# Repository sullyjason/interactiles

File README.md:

# Interactiles

[Portfolio Link](https://showspace.so/p/9350)

## Idea

Developing an interactive grid of buttons that light up and change colors when pressed, designed to communicate, connect, and create art across distances. Each grid is connected via the internet to a corresponding grid, allowing users to share visual messages in real-time.

## Prototyping

Until now, this project has served mostly as a platform for me to build on my coding and hardware skills. 

The current working prototype is a version with a 2x2 grid of RGB LED switches, connected to each other via an MQTT server.

The vision, of course, is a larger scale grid of clickable illuminated buttons. I am developing this with a modular approach, 4 tiles of 3x15 buttons controlled by a microcontroller that connects to the internet.

## To Do
- [x] Experiment with RGB Switches
- [x] Build hand-wired POC
- [x] Design PCB for 2x2 version
- [x] Assemble & test 2x2 version
- [x] Set up web server
- [x] Connect individual interactiles to web server
- [x] Web interface for monitoring
- [x] Large scale version module development (wip)
- [ ] Develop large scale version
- [ ] Design large scale modules
- [ ] Troubleshoot large scale modules
- [ ] Design miniature modules
- [ ] Enclosure for miniature modules
- [ ] Real world testing of 2x2 (in progress)

## Events

Exhibitions and real-world showings of Interactiles, each documented in its own folder under [`events/`](events/).

- [Zürich Decompression 2026](events/2026-decompression-zurich/) — two connected 5×3 grids in a fine-dining-inspired frame. Kraftwerk, Zürich, 9–11 October 2026.

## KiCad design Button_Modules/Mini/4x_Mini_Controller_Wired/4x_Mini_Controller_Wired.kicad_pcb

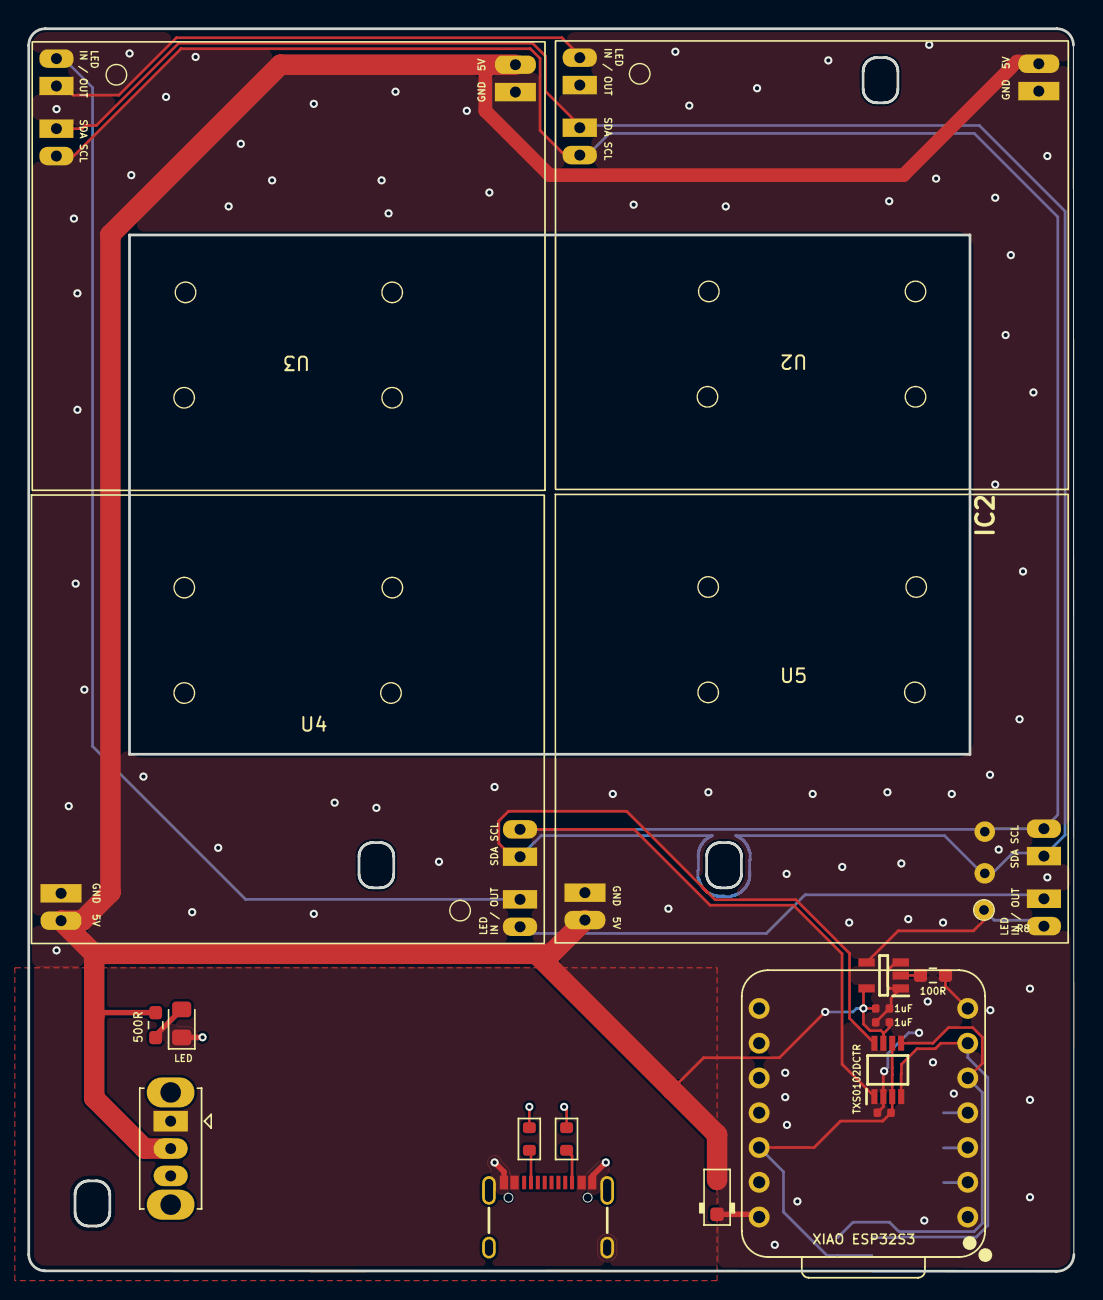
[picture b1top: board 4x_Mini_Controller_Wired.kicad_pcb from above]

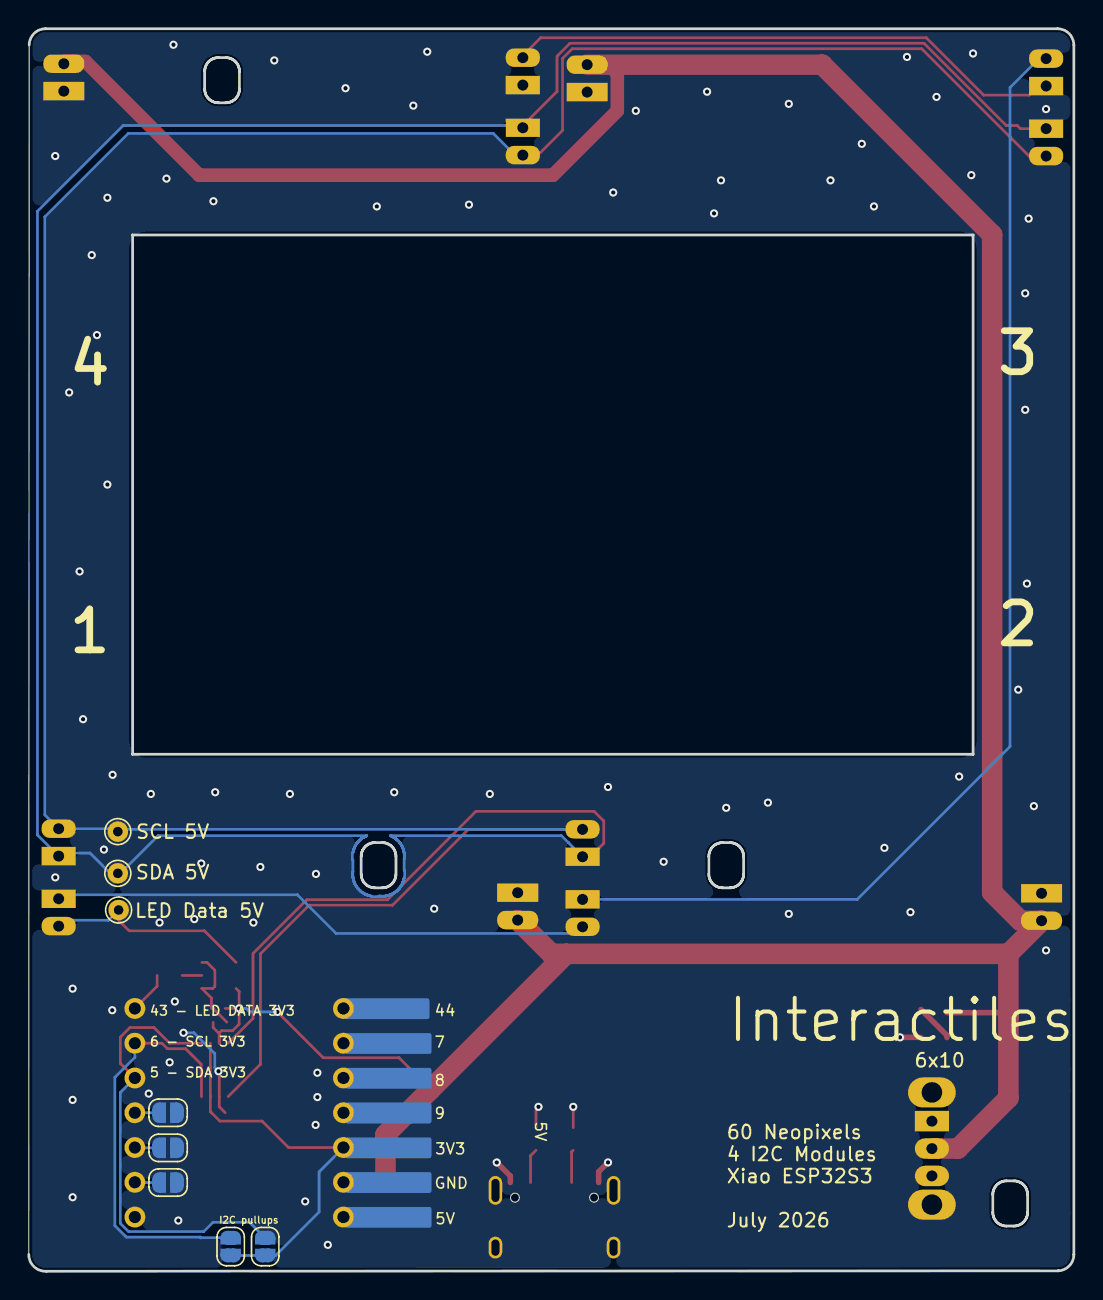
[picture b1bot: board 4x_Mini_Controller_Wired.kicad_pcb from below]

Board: 2 copper layers, 76.4 x 90.8 mm, 26 parts (8 on the bottom side), 21 nets.

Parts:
C2, C4, C7: 1uF; C_0402
D1: LED; LED_0805_2012Metric_Pad1.15x1.40mm_HandSolder
D6: 1N5817M; D_SOD-323_BigPads
IC2: TXS0102DCTR
IC3: SN74AHCT1G125DBVR
J2: USB_C_Receptacle; USB-C_16
JP1, JP2, JP5, JP6, JP7: SolderJumper_2_Open; SolderJumper-2_P1.3mm_Open_RoundedPad1.0x1.5mm
R1, R2: 5.1k; R_0603_1608Metric
R3: 500R; R_0603_1608Metric_Pad0.98x0.95mm_HandSolder
R8: 100R; R_0603_1608Metric_Pad0.98x0.95mm_HandSolder
SW5: Slide_Switch_SPDT; SW_Slide_SPDT_Straight_CK_OS102011MS2Q
TP3: SCL 5V; TestPoint_THTPad_D1.5mm_Drill0.7mm
TP4: SDA 5V; TestPoint_THTPad_D1.5mm_Drill0.7mm
TP5: LED Data 5V; TestPoint_THTPad_D1.5mm_Drill0.7mm
U2, U3, U4, U5: Mini_Module
U6: XIAO-ESP32-S3-SMD; XIAO-ESP32-S3-DIP

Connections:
+3V3: C4.1, IC2.3 (VCCA), IC2.6 (OE), JP6.2 (B), JP7.1 (A), U6.12 (3V3_OUT)
+5V: C2.1, C7.1, D6.2 (A), IC2.7 (VCCB), IC3.5 (VCC), R3.2, SW5.2, U2.5V, U3.5V, U4.5V, U5.5V
/5V to ESP32: D6.1 (K), U6.14 (VBUS)
/5V_TO_SWITCH: J2.VBUS, SW5.1
DATA_3v3: R8.1, U6.7 (D6)
DATA_5v: IC3.4 (Y), TP5.1 (1_1), U5.IN
DIP_1: JP1.1 (A), U6.2 (D1)
DIP_2: JP2.1 (A), U6.3 (D2)
DIP_3: JP5.1 (A), U6.4 (D3)
GND: C2.2, C4.2, C7.2, D1.1, IC2.2 (GND), IC3.1 (~OE), IC3.3 (GND), J2.GND, J2.S (SHIELD), JP1.2 (B), JP2.2 (B), JP5.2 (B), R1.2, R2.2, U2.GND, U3.GND, U4.GND, U5.GND, U6.13 (GND)
unnamed: D1.2, R3.1
unnamed: IC3.2 (A), R8.2
unnamed: J2.A5 (CC1), R1.1
unnamed: J2.B5 (CC2), R2.1
unnamed: U2.IN, U3.OUT
unnamed: U3.IN, U4.OUT
unnamed: U4.IN, U5.OUT
SCL_3v3: IC2.4 (A2), JP7.2 (B), U6.6 (D5)
SCL_5v: IC2.1 (B2), TP3.1 (1_1), U2.SCL, U3.SCL, U4.SCL, U5.SCL
SDA_3v3: IC2.5 (A1), JP6.1 (A), U6.5 (D4)
SDA_5v: IC2.8 (B1), TP4.1 (1_1), U2.SDA, U3.SDA, U4.SDA, U5.SDA

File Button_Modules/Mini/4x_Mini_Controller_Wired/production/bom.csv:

Designator,Footprint,Quantity,Value,LCSC Part #
"C2, C4, C7",C_0402,3,1uF,C52923
D1,0805,1,LED,
D6,D_SOD-323_BigPads,1,1N5817M,
IC2,TXS0102DCTR,1,TXS0102DCTR,
IC3,SN74AHCT1G125DBVR,1,SN74AHCT1G125DBVR,
J2,USB-C_16,1,USB_C_Receptacle,
"R1, R2",0603,2,5.1k,
R3,0603,1,500R,
R8,0603,1,100R,
SW5,SW_Slide_SPDT_Straight_CK_OS102011MS2Q,1,Slide_Switch_SPDT,
TP3,TestPoint_THTPad_D1.5mm_Drill0.7mm,1,SCL 5V,
TP4,TestPoint_THTPad_D1.5mm_Drill0.7mm,1,SDA 5V,
TP5,TestPoint_THTPad_D1.5mm_Drill0.7mm,1,LED Data 5V,
"U2, U3, U4, U5",Mini_Module,4,~,
U6,XIAO-ESP32-S3-DIP,1,XIAO-ESP32-S3-SMD,

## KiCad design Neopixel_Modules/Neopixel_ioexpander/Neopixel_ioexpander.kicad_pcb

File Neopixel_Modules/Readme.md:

# Modules of addressable RGB switch panels in various sizes

Configurations of 3x5 Switches to create a 15 pixel grid, listening for key interrupts via an MCP23017 i2c I/O expander. The switches are provided by Lakeview Electronics in Shenzhen. They are invididually addressable and compatible with the Neopixel library. 

## Large

Using the largest assembly of the manufacturer's PLB product line, measuring alost 3x3cm per switch. 15 switches routed to a FCP Connector, headers for LED data lines and screw terminals for 5V/ground.

## I/O Expander

Using a MCP23017. For use with the large module via the FPC connector or for other future switch modules. Reduces the 15 individual switch lines to two i2c lines. Using a dip switch to set the i2c address.

https://learn.adafruit.com/adafruit-mcp23017-i2c-gpio-expander
https://github.com/adafruit/Adafruit-MCP23017-Arduino-Library

## Mini

Using the smallest assembly of the manufacturer's TL1 product line, measuring only 7.5mm^2 per switch. the module is so tightly packed that the PCB had to be designed in 4 layers and the i/o expander is directly attached to the bottom of the switch grid. 
Pinout on i/o expander is not intuitive as a result, refer to schematic. 

## Controller (WIP)

Controller for a string of a maximum of 8 3x5 modules, using an ESP32.
- ESP32
- interfaces: i2c, LED data, common ground
- Charger, if battery power is used (make optional?) and USB-C port with PD circuit?
- On/off switch and small LED indicator
- Toggle switch for "Set" or "program" mode for configuration
- ?

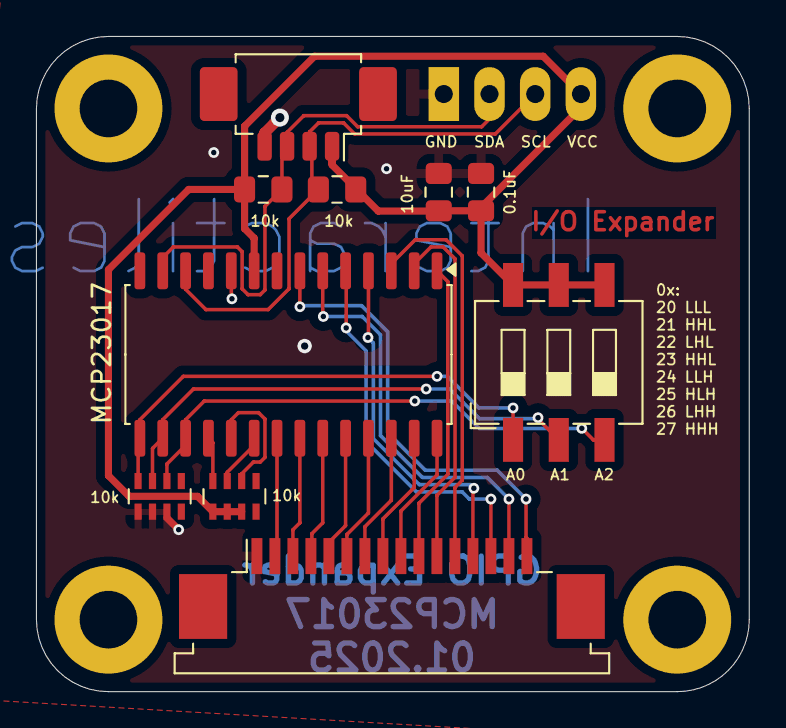
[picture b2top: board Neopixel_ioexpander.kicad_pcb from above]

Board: 2 copper layers, 39.6 x 36.4 mm, 15 parts (0 on the bottom side), 25 nets.

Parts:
0.1uF: 0.1uF; C_0805_2012Metric_Pad1.18x1.45mm_HandSolder
10k, 10k#2: R_Pack04; R_Array_Concave_4x0603
10k#3, 10k#4: 10k; C_0805_2012Metric_Pad1.18x1.45mm_HandSolder
10uF: 10uF; C_0805_2012Metric_Pad1.18x1.45mm_HandSolder
H1, H2, H3, H4: MountingHole_M3_3.2mm_Pad; MountingHole_3.2mm_Pad
J1: PINHD_1x16_Male; TE_1-84952-6_1x16-1MP_P1.0mm_Horizontal
J2: PINHD_1x4_Male; Molex_PicoBlade_53261-0471_1x04-1MP_P1.25mm_Horizontal
J3: PINHD_1x4_Male; PinHeader_1x04_P2.54mm_Vertical
MCP23017: MCP23017_SO; SOIC-28W_7.5x17.9mm_P1.27mm
SW2: SW_DIP_x03; SW_DIP_SPSTx03_Slide_6.7x9.18mm_W8.61mm_P2.54mm_LowProfile

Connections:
GND: 0.1uF.2, 10k#2.1 (R1.1), 10k#2.2 (R2.1), 10k#2.3 (R3.1), 10uF.2, J1.1, J2.4, J3.4, MCP23017.10 (VSS)
unnamed: 10k.2 (R2.1), MCP23017.19 (INTB)
unnamed: 10k.3 (R3.1), MCP23017.20 (INTA)
unnamed: 10k.4 (R4.1), MCP23017.18 (~RESET)
unnamed: 10k#2.8 (R1.2), MCP23017.15 (A0), SW2.1
unnamed: 10k#2.7 (R2.2), MCP23017.16 (A1), SW2.2
unnamed: 10k#2.6 (R3.2), MCP23017.17 (A2), SW2.3
SCL: 10k#4.1, J2.2, J3.2, MCP23017.12 (SCK)
SDA: 10k#3.1, J2.3, J3.3, MCP23017.13 (SDA)
SW1: J1.2, MCP23017.21 (GPA0)
SW2: J1.3, MCP23017.22 (GPA1)
SW3: J1.4, MCP23017.23 (GPA2)
SW4: J1.5, MCP23017.24 (GPA3)
SW5: J1.6, MCP23017.25 (GPA4)
SW6: J1.7, MCP23017.26 (GPA5)
SW7: J1.8, MCP23017.27 (GPA6)
SW8: J1.9, MCP23017.28 (GPA7)
SW9: J1.10, MCP23017.1 (GPB0)
SW10: J1.11, MCP23017.2 (GPB1)
SW11: J1.12, MCP23017.3 (GPB2)
SW12: J1.13, MCP23017.4 (GPB3)
SW13: J1.14, MCP23017.5 (GPB4)
SW14: J1.15, MCP23017.6 (GPB5)
SW15: J1.16, MCP23017.7 (GPB6)
VCC: 0.1uF.1, 10k.5 (R4.2), 10k.6 (R3.2), 10k.7 (R2.2), 10k#3.2, 10k#4.2, 10uF.1, J2.1, J3.1, MCP23017.9 (VDD), SW2.4, SW2.5, SW2.6

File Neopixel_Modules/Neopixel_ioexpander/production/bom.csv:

Designator,Footprint,Quantity,Value,LCSC Part #
0.1uF,0805,1,0.1uF,
"10k_4, 10k_3",R_Array_Concave_4x0603,2,R_Pack04,
"10k_2, 10k",0805,2,10k,
10uF,0805,1,10uF,
"H1, H2, H3, H4",MountingHole_3.2mm_Pad,4,MountingHole_M3_3.2mm_Pad,
J1,TE_1-84952-6_1x16-1MP_P1.0mm_Horizontal,1,PINHD_1x16_Male,
J2,Molex_PicoBlade_53261-0471_1x04-1MP_P1.25mm_Horizontal,1,PINHD_1x4_Male,
J3,PinHeader_1x04_P2.54mm_Vertical,1,PINHD_1x4_Male,
MCP23017,SOIC-28W_7.5x18.7mm_P1.27mm,1,MCP23017_ML,
SW2,SW_DIP_SPSTx03_Slide_6.7x9.18mm_W8.61mm_P2.54mm_LowProfile,1,SW_DIP_x03,

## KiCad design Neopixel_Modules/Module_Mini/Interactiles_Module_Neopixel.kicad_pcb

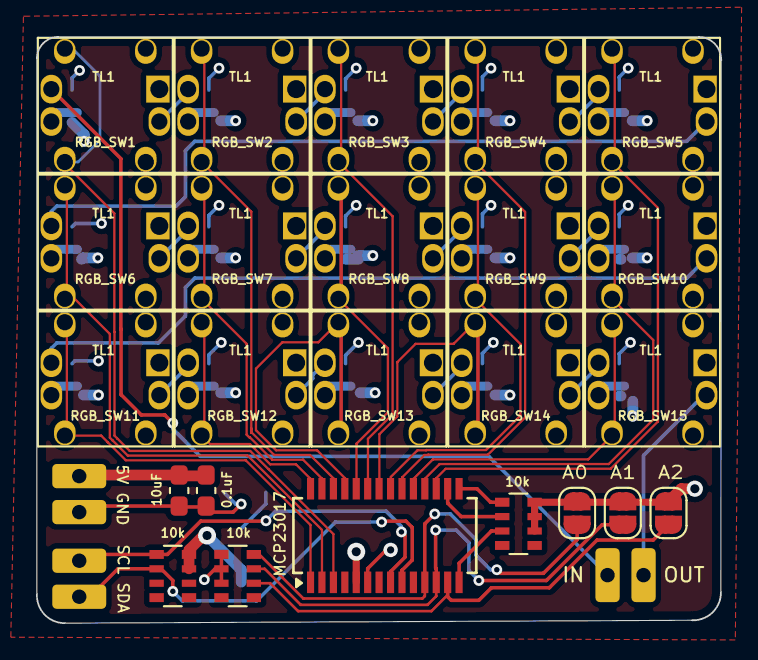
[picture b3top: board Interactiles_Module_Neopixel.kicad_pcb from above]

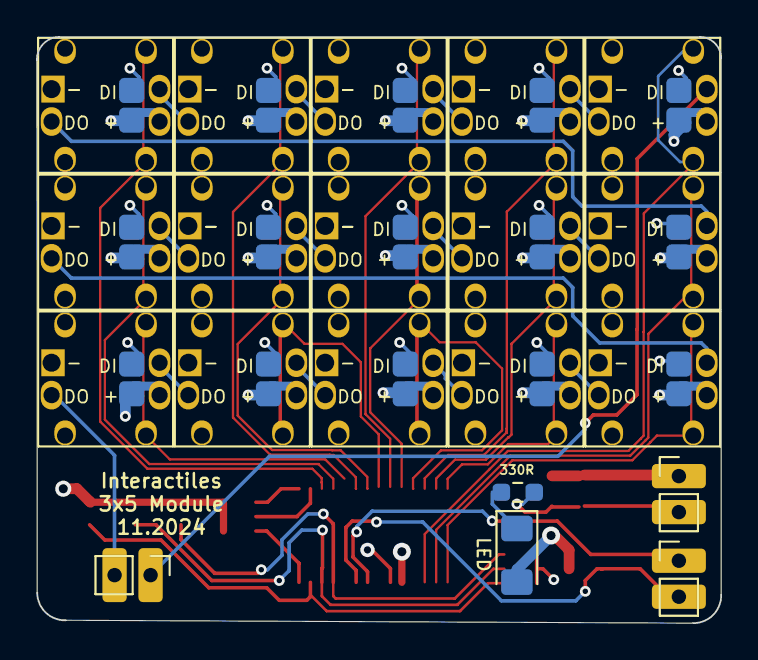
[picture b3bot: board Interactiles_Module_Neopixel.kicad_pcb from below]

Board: 4 copper layers, 38.0 x 32.6 mm, 29 parts (5 on the bottom side), 42 nets.

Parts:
10k, 10k#2: R_Pack04; R_Array_Convex_4x0603
C1: 10uF; C_0603_1608Metric_Pad1.08x0.95mm_HandSolder
C2: 0.1uF; C_0603_1608Metric_Pad1.08x0.95mm_HandSolder
J1: PINHD_1x2_Male; PinHeader_1x02_P2.00mm_Vertical
J2, J4: PINHD_1x2_Female; PinHeader_1x02_P2.00mm_Vertical
JP1, JP2, JP3: SolderJumper_2_Open; SolderJumper-2_P1.3mm_Open_RoundedPad1.0x1.5mm
LED: LED; LED_1206_3216Metric_Pad1.42x1.75mm_HandSolder
R1: 330R; R_0603_1608Metric_Pad0.98x0.95mm_HandSolder
RGB_SW1, RGB_SW2, RGB_SW3, RGB_SW4, RGB_SW5, RGB_SW6, RGB_SW7, RGB_SW8, RGB_SW9, RGB_SW10, RGB_SW11, RGB_SW12, RGB_SW13, RGB_SW14, RGB_SW15: PLB_RGB_SW; TL1_RBG_Adressable_1_mini
RN2: R_Pack04; R_Array_Convex_4x0603
U1: MCP23017_ML; SSOP-28_3.9x9.9mm_P0.635mm

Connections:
+5V: 10k.7 (R2.2), 10k.8 (R1.2), C1.1, C2.1, J1.1, JP1.2 (B), JP2.2 (B), JP3.2 (B), LED.2, RGB_SW1.VDD, RGB_SW2.VDD, RGB_SW3.VDD, RGB_SW4.VDD, RGB_SW5.VDD, RGB_SW6.VDD, RGB_SW7.VDD, RGB_SW8.VDD, RGB_SW9.VDD, RGB_SW10.VDD, RGB_SW11.VDD, RGB_SW12.VDD, RGB_SW13.VDD, RGB_SW14.VDD, RGB_SW15.VDD, RN2.6 (R3.2), RN2.7 (R2.2), RN2.8 (R1.2), U1.5 (VDD)
GND: 10k#2.1 (R1.1), 10k#2.2 (R2.1), 10k#2.3 (R3.1), C1.2, C2.2, J1.2, R1.2, RGB_SW1.GND, RGB_SW1.SW2, RGB_SW2.GND, RGB_SW2.SW2, RGB_SW3.GND, RGB_SW3.SW2, RGB_SW4.GND, RGB_SW4.SW2, RGB_SW5.GND, RGB_SW5.SW2, RGB_SW6.GND, RGB_SW6.SW2, RGB_SW7.GND, RGB_SW7.SW2, RGB_SW8.GND, RGB_SW8.SW2, RGB_SW9.GND, RGB_SW9.SW2, RGB_SW10.GND, RGB_SW10.SW2, RGB_SW11.GND, RGB_SW11.SW2, RGB_SW12.GND, RGB_SW12.SW2, RGB_SW13.GND, RGB_SW13.SW2, RGB_SW14.GND, RGB_SW14.SW2, RGB_SW15.GND, RGB_SW15.SW2, U1.6 (VSS)
LED_IN: J4.1, RGB_SW1.DI (DIN)
LED_OUT: J4.2, RGB_SW15.DO
unnamed: LED.1, R1.1
unnamed: 10k#2.8 (R1.2), JP1.1 (A), U1.11 (A0)
unnamed: 10k#2.7 (R2.2), JP2.1 (A), U1.12 (A1)
unnamed: 10k#2.6 (R3.2), JP3.1 (A), U1.13 (A2)
unnamed: RGB_SW1.DO, RGB_SW2.DI (DIN)
unnamed: RGB_SW2.DO, RGB_SW3.DI (DIN)
unnamed: RGB_SW3.DO, RGB_SW4.DI (DIN)
unnamed: RGB_SW4.DO, RGB_SW5.DI (DIN)
unnamed: RGB_SW5.DO, RGB_SW6.DI (DIN)
unnamed: RGB_SW6.DO, RGB_SW7.DI (DIN)
unnamed: RGB_SW7.DO, RGB_SW8.DI (DIN)
unnamed: RGB_SW8.DO, RGB_SW9.DI (DIN)
unnamed: RGB_SW9.DO, RGB_SW10.DI (DIN)
unnamed: RGB_SW10.DO, RGB_SW11.DI (DIN)
unnamed: RGB_SW11.DO, RGB_SW12.DI (DIN)
unnamed: RGB_SW12.DO, RGB_SW13.DI (DIN)
unnamed: RGB_SW13.DO, RGB_SW14.DI (DIN)
unnamed: RGB_SW14.DO, RGB_SW15.DI (DIN)
unnamed: RN2.1 (R1.1), U1.15 (INTB)
unnamed: RN2.2 (R2.1), U1.16 (INTA)
unnamed: RN2.3 (R3.1), U1.14 (~RESET)
SCL: 10k.1 (R1.1), J2.1, U1.8 (SCK)
SDA: 10k.2 (R2.1), J2.2, U1.9 (SDA)
SW1: RGB_SW1.SW1, U1.3 (GPB6)
SW2: RGB_SW2.SW1, U1.26 (GPB1)
SW3: RGB_SW3.SW1, U1.23 (GPA6)
SW4: RGB_SW4.SW1, U1.20 (GPA3)
SW5: RGB_SW5.SW1, U1.17 (GPA0)
SW6: RGB_SW6.SW1, U1.2 (GPB5)
SW7: RGB_SW7.SW1, U1.27 (GPB2)
SW8: RGB_SW8.SW1, U1.24 (GPA7)
SW9: RGB_SW9.SW1, U1.21 (GPA4)
SW10: RGB_SW10.SW1, U1.18 (GPA1)
SW11: RGB_SW11.SW1, U1.1 (GPB4)
SW12: RGB_SW12.SW1, U1.28 (GPB3)
SW13: RGB_SW13.SW1, U1.25 (GPB0)
SW14: RGB_SW14.SW1, U1.22 (GPA5)
SW15: RGB_SW15.SW1, U1.19 (GPA2)

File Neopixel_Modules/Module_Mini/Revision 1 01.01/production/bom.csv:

Designator,Footprint,Quantity,Value,LCSC Part #
0.1uF,0603,1,0.1uF,
10uF,0805,1,10uF,
J1,PinHeader_1x02_P2.00mm_Vertical,1,PINHD_1x2_Male,
"J2, J4",PinHeader_1x02_P2.00mm_Vertical,2,PINHD_1x2_Female,
LED,0603,1,LED,
MCP23017,SSOP-28_5.3x10.2mm_P0.65mm,1,MCP23017_SS,
R1,0603,1,330R,
"RGB_SW1, RGB_SW10, RGB_SW11, RGB_SW12, RGB_SW13, RGB_SW14, RGB_SW15, RGB_SW2, RGB_SW3, RGB_SW4, RGB_SW5, RGB_SW6, RGB_SW7, RGB_SW8, RGB_SW9",TL1_RBG_Adressable_1_mini,15,PLB_RGB_SW,
"RN1, RN2, RN3",R_Array_Convex_4x0603,3,R_Pack04,

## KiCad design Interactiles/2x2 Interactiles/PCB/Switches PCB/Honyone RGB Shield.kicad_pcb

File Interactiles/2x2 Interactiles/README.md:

readme.md

# 2x2 Interactile

Device with a 2x2 matrix of RGB Switches, controlled by an ESP32. The switches are arranged in a matrix configuration. WS2811 IC's control the RGB LEDs embedded in the switches, controlled using the Adafruit Neopixel library. 

The enclosure is 3D printed in PLA with an acrylic backplate, secured with M2 screws and a knurled nut to allow for easy battery switching. 

The battery is a CR123 sized 3.7 Li-Ion and provides the entire device with power. A polarity protection circuit protects the PCB but there is no charging circuit. 

### Interfacing via MQTT

The current code in the folder named "MQTT" connects the interactiles to an MQTT server, where they publish and subscribe to channels that correspond to the individual pixels. 

The server is located at 
```c++
mqtt_server = "test.mosquitto.org";
mqtt_port = 1883;
base_topic = "interactiles/space1";
```

Configure Wifi settings here
```C++
// Wi-Fi credentials
const char* ssid = "SSID";
const char* password = "PASSWORD";
```

The channel structure is as follows:
interactiles/space[]/row/col/r,g,b

The space ID is currently hardcoded. In future versions it should be possible to set this via a DIP switch or similar.

row and column are matched to a specific RGB Switch as follows:
```c++
int mapToLedIndex(int row, int col) {
  if (row == 1 && col == 1) return 0;
  if (row == 1 && col == 2) return 2;
  if (row == 2 && col == 1) return 1;
  if (row == 2 && col == 2) return 3;
  return -1;
}
```

## Future changes
 
- Current version uses WS2811 LED drivers. Replace with intelligent RGB LED Switches
- Improve power management: Use xiao ESP32S3's onboard charging or redesign charging circuit. Alternatively, completely elminate wireless option
- Fix dip switch behavior
- Spaces architecture: The idea of spaces is that multiple devices can exist in the same space and be a part of the same image. Idea for naming: space1.1, space 1.2, etc.
- Hardcode meta data on each device and have the devices respond to each other accordingly
- MQTT or wifi connecting animation for improved usability
- consider creating a docking station
- Add wifi manager library

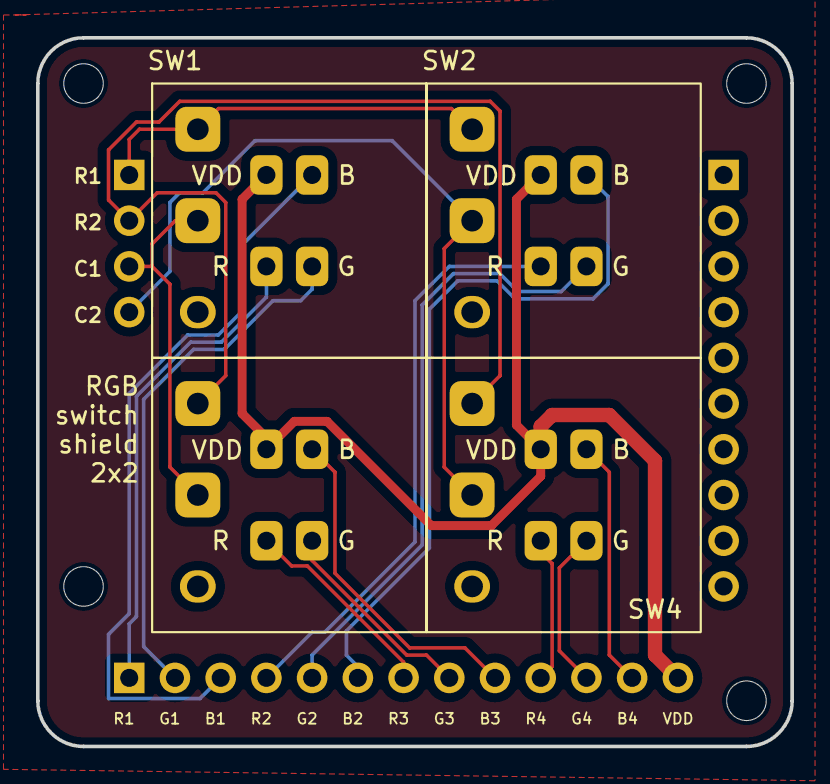
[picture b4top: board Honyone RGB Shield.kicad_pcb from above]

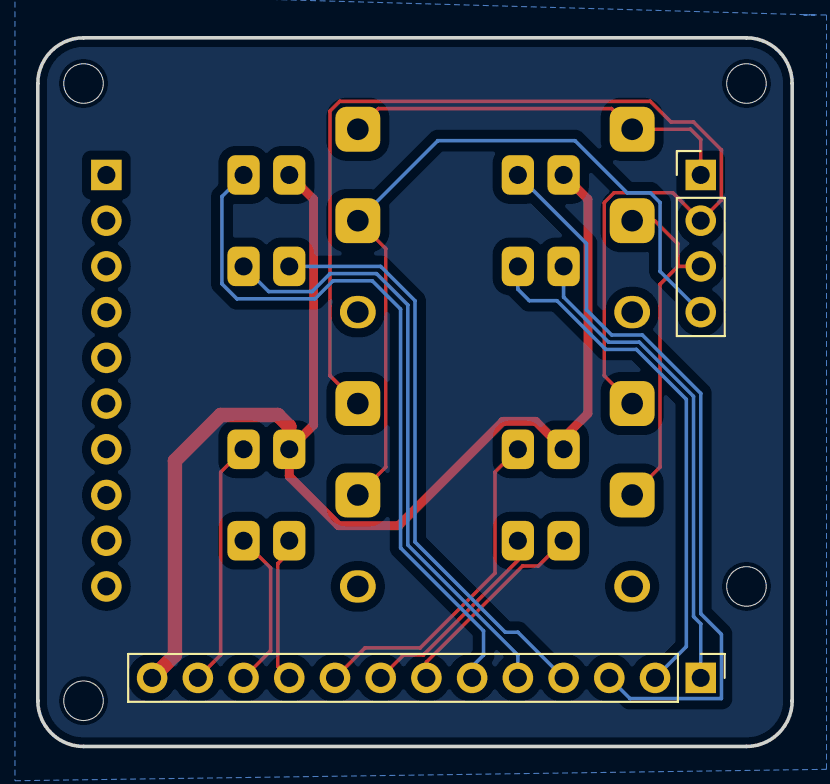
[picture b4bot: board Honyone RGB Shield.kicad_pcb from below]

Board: 2 copper layers, 41.9 x 39.4 mm, 6 parts (2 on the bottom side), 17 nets.

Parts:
J1: PINHD_1x4_Male; PinHeader_1x04_P2.54mm_Vertical
J2: PINHD_1x13_Male; PinHeader_1x13_P2.54mm_Vertical
SW1: RGB_SW_1; Honyone Tactile Switch RGB
SW2: RGB_SW_2; Honyone Tactile Switch RGB
SW3: RGB_SW_3; Honyone Tactile Switch RGB
SW4: RGB_SW_4; Honyone Tactile Switch RGB

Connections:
B1: J2.3, SW1.B
B2: J2.6, SW2.B
B3: J2.9, SW3.B
B4: J2.12, SW4.B
Col1: J1.3, SW1.1, SW3.1
Col2: J1.4, SW2.1, SW4.1
G1: J2.2, SW1.G
G2: J2.5, SW2.G
G3: J2.8, SW3.G
G4: J2.11, SW4.G
R1: J2.1, SW1.R
R2: J2.4, SW2.R
R3: J2.7, SW3.R
R4: J2.10, SW4.R
Row1: J1.1, SW1.2, SW2.2
Row2: J1.2, SW3.2, SW4.2
VDD: J2.13, SW1.VDD, SW2.VDD, SW3.VDD, SW4.VDD

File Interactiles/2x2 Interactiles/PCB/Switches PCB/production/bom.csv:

Designator,Footprint,Quantity,Value,LCSC Part #
J1,PinHeader_1x04_P2.54mm_Vertical,1,PINHD_1x4_Male,
J2,PinHeader_1x13_P2.54mm_Vertical,1,PINHD_1x13_Male,
SW1,Honyone Tactile Switch RGB,1,RGB_SW_1,
SW2,Honyone Tactile Switch RGB,1,RGB_SW_2,
SW3,Honyone Tactile Switch RGB,1,RGB_SW_3,
SW4,Honyone Tactile Switch RGB,1,RGB_SW_4,

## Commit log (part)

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2024-09-11 Create Offline_2x2
2024-11-05 added
2024-11-05 added large module files
2024-11-05 Added Controller Package
2024-11-05 added files
2024-11-17 updated IO expander to bigger MCP23017 footprint
2024-11-23 backups
2024-11-23 replaced picoblade connectors with THT pads, moved some stuff around
2024-11-27 fixed for pcb production
2025-01-01 PCB Revisions
    MCP23017 had incorrect footprints, some tolerances between pads were too tight (shorts), resized some components
2025-05-17 Fixed GRB to RGB 2x2_XiaoESP32C3.ino
2025-08-22 Added initial MQTT code
2025-09-07 Updated Readme, added channel structure explanation
2025-09-07 fixed diagram
2025-12-14 Upload correct code
    added some to-dos. Debug connectivity issues
